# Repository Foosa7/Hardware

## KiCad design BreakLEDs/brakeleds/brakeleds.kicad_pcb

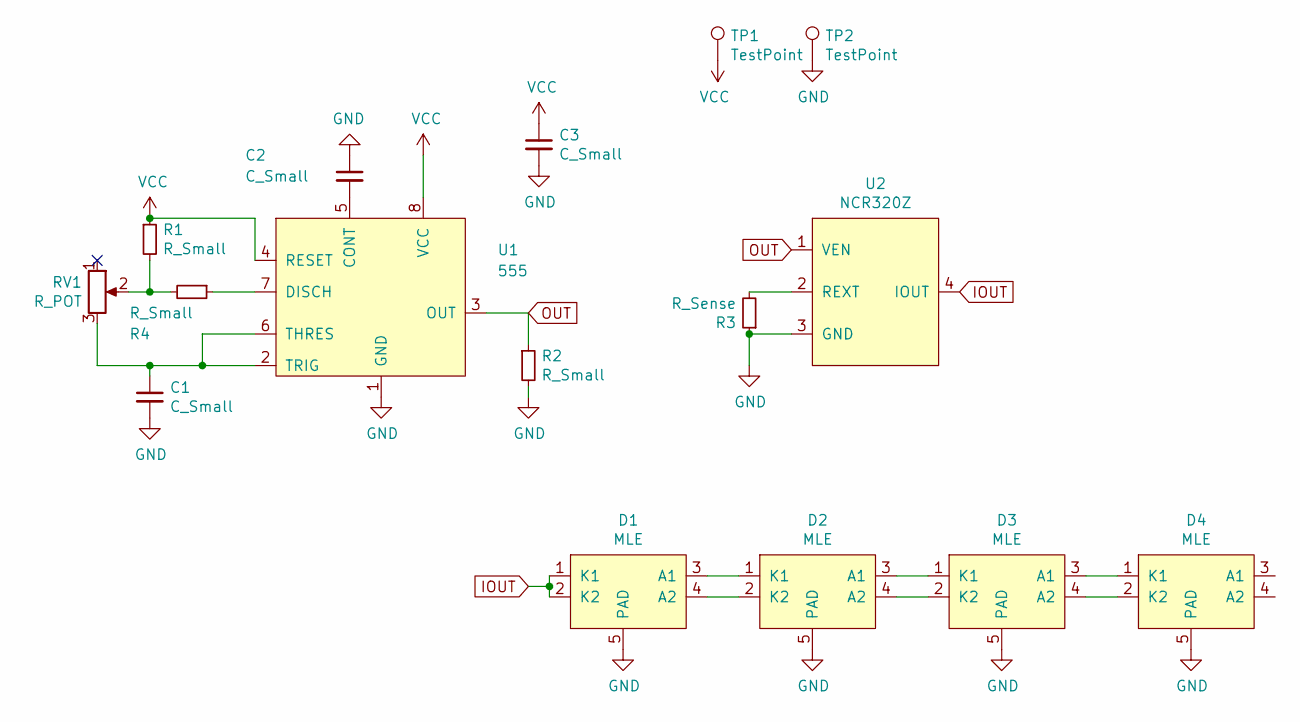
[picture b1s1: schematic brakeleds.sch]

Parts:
C1, C2, C3: C_Small; C_0603_1608Metric
D1, D2, D3, D4: MLE; PLCC-4
R1, R2, R4: R_Small; R_0603_1608Metric
R3: R_Sense; R_0805_2012Metric
RV1: R_POT; potentiometer
TP1, TP2: TestPoint; SolderWirePad_1x01_SMD_1x2mm
U1: 555; TSSOP-8_4.4x3mm_P0.65mm
U2: NCR320Z; SOT-223

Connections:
GND: C1.2, C2.1, C3.2, D1.5 (PAD), D2.5 (PAD), D3.5 (PAD), D4.5 (PAD), R2.2, R3.1, TP2.1, U1.1 (GND), U2.3 (GND)
IOUT: D1.1 (K1), D1.2 (K2), U2.4 (IOUT)
unnamed: C1.1, RV1.3, U1.2 (TRIG), U1.6 (THRES)
unnamed: C2.2, U1.5 (CONT)
unnamed: D1.3 (A1), D2.1 (K1)
unnamed: D1.4 (A2), D2.2 (K2)
unnamed: D2.3 (A1), D3.1 (K1)
unnamed: D2.4 (A2), D3.2 (K2)
unnamed: D3.3 (A1), D4.1 (K1)
unnamed: D3.4 (A2), D4.2 (K2)
unnamed: R1.2, R4.2, RV1.2
unnamed: R3.2, U2.2 (REXT)
unnamed: R4.1, U1.7 (DISCH)
OUT: R2.1, U1.3 (OUT), U2.1 (VEN)
VCC: C3.1, R1.1, TP1.1, U1.4 (RESET), U1.8 (VCC)

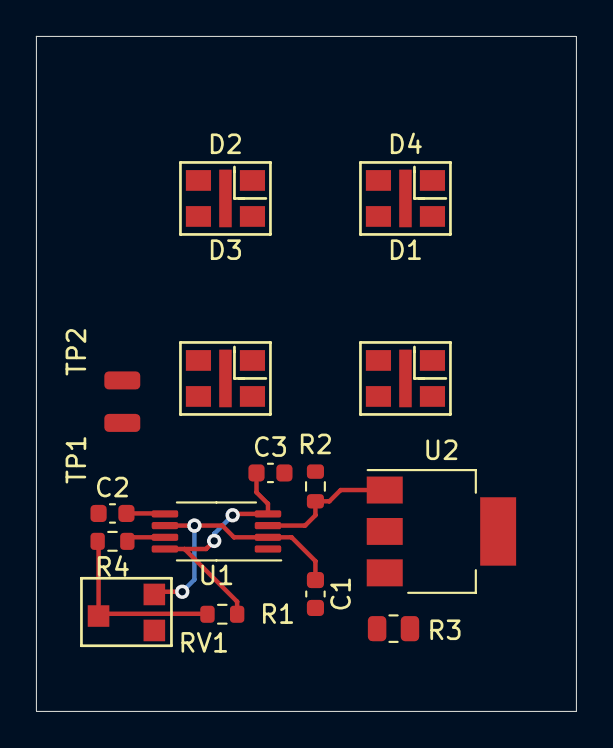
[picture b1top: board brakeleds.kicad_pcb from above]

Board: 2 copper layers, 30.0 x 37.5 mm, 16 parts (0 on the bottom side), 15 nets.

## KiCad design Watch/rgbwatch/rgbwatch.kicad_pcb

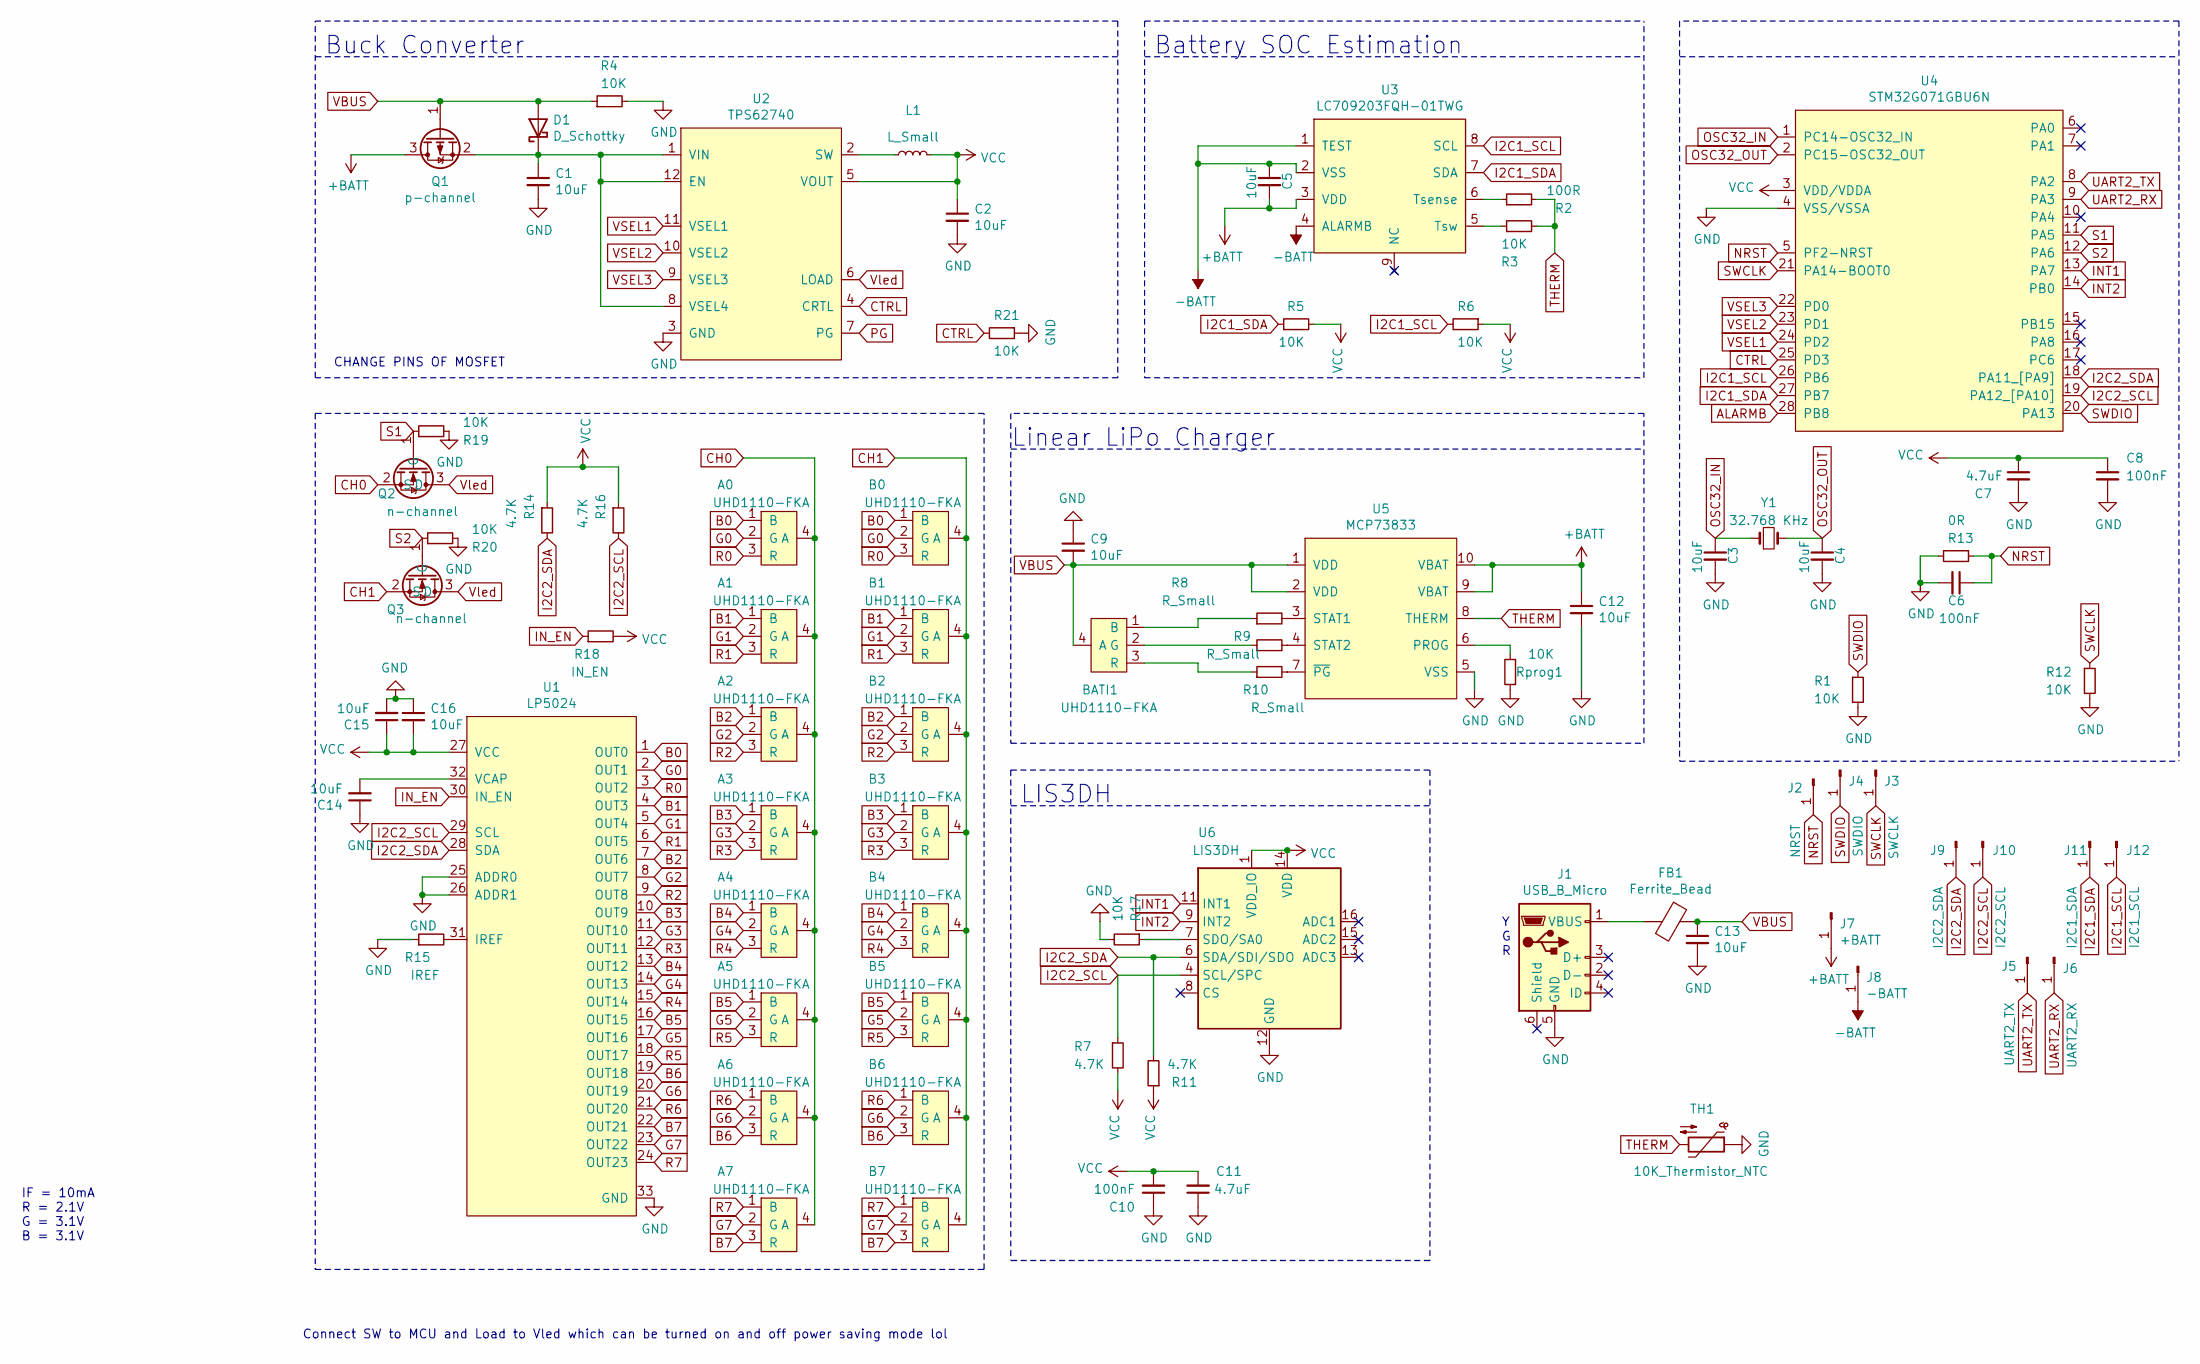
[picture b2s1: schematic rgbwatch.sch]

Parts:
A0, A1, A2, A3, A4, A5, A6, A7: UHD1110-FKA
B0, B1, B2, B3, B4, B5, B6, B7: UHD1110-FKA
BATI1: UHD1110-FKA
C1, C2, C3, C4, C5, C9, C12, C13, C14, C15, C16: 10uF; C_0402_1005Metric
C6, C8, C10: 100nF; C_0402_1005Metric
C7, C11: 4.7uF; C_0402_1005Metric
D1: D_Schottky; D_SOD-123
FB1: Ferrite_Bead; L_0603_1608Metric
J1: USB_B_Micro; USB_Micro-B_Amphenol_10104110_Horizontal
J2: NRST; SolderWirePad_1x01_SMD_1x2mm
J3: SWCLK; SolderWirePad_1x01_SMD_1x2mm
J4: SWDIO; SolderWirePad_1x01_SMD_1x2mm
J5: UART2_TX; SolderWirePad_1x01_SMD_1x2mm
J6: UART2_RX; SolderWirePad_1x01_SMD_1x2mm
J7: +BATT; SolderWirePad_1x01_SMD_1x2mm
J8: -BATT; SolderWirePad_1x01_SMD_1x2mm
J9: I2C2_SDA; SolderWirePad_1x01_SMD_1x2mm
J10: I2C2_SCL; SolderWirePad_1x01_SMD_1x2mm
J11: I2C1_SDA; SolderWirePad_1x01_SMD_1x2mm
J12: I2C1_SCL; SolderWirePad_1x01_SMD_1x2mm
L1: L_Small; L_0805_2012Metric
Q1: p-channel; SOT-23
Q2, Q3: n-channel; SOT-23
R1, R3, R4, R5, R6, R12, R17, R19, R20, R21: 10K; R_0402_1005Metric
R2: 100R; R_0402_1005Metric
R7, R11, R14, R16: 4.7K; R_0402_1005Metric
R8, R9, R10: R_Small; R_0402_1005Metric
R13: 0R; R_0402_1005Metric
R15: IREF; R_0402_1005Metric
R18: IN_EN; R_0402_1005Metric
Rprog1: 10K; R_0402_1005Metric
TH1: 10K_Thermistor_NTC; R_0603_1608Metric
U1: LP5024; QFN-32_EP_4.4x4.4_Pitch0.4mm
U2: TPS62740; WSON-12-1EP_3x2mm_P0.5mm_EP1x2.65_ThermalVias
U3: LC709203FQH−01TWG; WDFN-8
U4: STM32G071GBU6N; QFN-28_EP_5.3x5.3_Pitch0.5mm
U5: MCP73833; DFN-10-1EP_3x3mm_P0.5mm_EP1.65x2.38mm_ThermalVias
U6: LIS3DH; LGA-16_3x3mm_P0.5mm_LayoutBorder3x5y
Y1: 32.768 KHz; Crystal_SMD_2012-2Pin_2.0x1.2mm

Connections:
+BATT: C5.2, C12.1, J7.1, Q1.3 (D), U3.3 (VDD), U5.9 (VBAT), U5.10 (VBAT)
-BATT: C5.1, J8.1, U3.1 (TEST), U3.2 (VSS), U3.4 (ALARMB)
ALARMB: U4.28 (PB8)
B0: A0.1 (B), B0.1 (B), U1.1 (OUT0)
B1: A1.1 (B), B1.1 (B), U1.4 (OUT3)
B2: A2.1 (B), B2.1 (B), U1.7 (OUT6)
B3: A3.1 (B), B3.1 (B), U1.10 (OUT9)
B4: A4.1 (B), B4.1 (B), U1.13 (OUT12)
B5: A5.1 (B), B5.1 (B), U1.16 (OUT15)
B6: A6.3 (R), B6.3 (R), U1.19 (OUT18)
B7: A7.3 (R), B7.3 (R), U1.22 (OUT21)
CH0: A0.4 (A), A1.4 (A), A2.4 (A), A3.4 (A), A4.4 (A), A5.4 (A), A6.4 (A), A7.4 (A), Q2.2 (S)
CH1: B0.4 (A), B1.4 (A), B2.4 (A), B3.4 (A), B4.4 (A), B5.4 (A), B6.4 (A), B7.4 (A), Q3.2 (S)
CTRL: R21.2, U2.4 (CRTL), U4.25 (PD3)
G0: A0.2 (G), B0.2 (G), U1.2 (OUT1)
G1: A1.2 (G), B1.2 (G), U1.5 (OUT4)
G2: A2.2 (G), B2.2 (G), U1.8 (OUT7)
G3: A3.2 (G), B3.2 (G), U1.11 (OUT10)
G4: A4.2 (G), B4.2 (G), U1.14 (OUT13)
G5: A5.2 (G), B5.2 (G), U1.17 (OUT16)
G6: A6.2 (G), B6.2 (G), U1.20 (OUT19)
G7: A7.2 (G), B7.2 (G), U1.23 (OUT22)
GND: C1.2, C2.2, C3.2, C4.2, C6.2, C7.2, C8.2, C9.1, C10.1, C11.1, C12.2, C13.2, C14.1, C15.2, C16.1, J1.5 (GND), R1.2, R4.2, R12.2, R13.2, R15.1, R17.2, R19.2, R20.2, R21.1, Rprog1.1, TH1.1, U1.25 (ADDR0), U1.26 (ADDR1), U1.33 (GND), U2.3 (GND), U4.4 (VSS/VSSA), U5.5 (VSS), U6.5 (GND), U6.10 (GND), U6.12 (GND)
I2C1_SCL: J12.1, R6.2, U3.8 (SCL), U4.26 (PB6)
I2C1_SDA: J11.1, R5.1, U3.7 (SDA), U4.27 (PB7)
I2C2_SCL: J10.1, R7.1, R16.2, U1.29 (SCL), U4.19 (PA12_[PA10]), U6.4 (SCL/SPC)
I2C2_SDA: J9.1, R11.2, R14.2, U1.28 (SDA), U4.18 (PA11_[PA9]), U6.6 (SDA/SDI/SDO)
INT1: U4.13 (PA7), U6.11 (INT1)
INT2: U4.14 (PB0), U6.9 (INT2)
IN_EN: R18.1, U1.30 (IN_EN)
NRST: C6.1, J2.1, R13.1, U4.5 (PF2-NRST)
unnamed: BATI1.1 (B), R8.1
unnamed: BATI1.2 (G), R9.1
unnamed: BATI1.3 (R), R10.1
unnamed: C1.1, D1.1 (K), Q1.2 (S), U2.1 (VIN), U2.8 (VSEL4), U2.12 (EN)
unnamed: C14.2, U1.32 (VCAP)
unnamed: FB1.2, J1.1 (VBUS)
unnamed: L1.1, U2.2 (SW)
unnamed: R2.1, U3.6 (Tsense)
unnamed: R3.1, U3.5 (Tsw)
unnamed: R8.2, U5.3 (STAT1)
unnamed: R9.2, U5.4 (STAT2)
unnamed: R10.2, U5.7 (~PG)
unnamed: R15.2, U1.31 (IREF)
unnamed: R17.1, U6.7 (SDO/SA0)
unnamed: Rprog1.2, U5.6 (PROG)
OSC32_IN: C3.1, U4.1 (PC14-OSC32_IN), Y1.1
OSC32_OUT: C4.1, U4.2 (PC15-OSC32_OUT), Y1.2
PG: U2.7 (PG)
R0: A0.3 (R), B0.3 (R), U1.3 (OUT2)
R1: A1.3 (R), B1.3 (R), U1.6 (OUT5)
R2: A2.3 (R), B2.3 (R), U1.9 (OUT8)
R3: A3.3 (R), B3.3 (R), U1.12 (OUT11)
R4: A4.3 (R), B4.3 (R), U1.15 (OUT14)
R5: A5.3 (R), B5.3 (R), U1.18 (OUT17)
R6: A6.1 (B), B6.1 (B), U1.21 (OUT20)
R7: A7.1 (B), B7.1 (B), U1.24 (OUT23)
S1: Q2.1 (G), R19.1, U4.11 (PA5)
S2: Q3.1 (G), R20.1, U4.12 (PA6)
SWCLK: J3.1, R12.1, U4.21 (PA14-BOOT0)
SWDIO: J4.1, R1.1, U4.20 (PA13)
THERM: R2.2, R3.2, TH1.2, U5.8 (THERM)
UART2_RX: J6.1, U4.9 (PA3)
UART2_TX: J5.1, U4.8 (PA2)
VBUS: BATI1.4 (A), C9.2, C13.1, D1.2 (A), FB1.1, Q1.1 (G), R4.1, U5.1 (VDD), U5.2 (VDD)
VCC: C2.1, C7.1, C8.1, C10.2, C11.2, C15.1, C16.2, L1.2, R5.2, R6.1, R7.2, R11.1, R14.1, R16.1, R18.2, U1.27 (VCC), U2.5 (VOUT), U4.3 (VDD/VDDA), U6.1 (VDD_IO), U6.14 (VDD)
VSEL1: U2.11 (VSEL1), U4.24 (PD2)
VSEL2: U2.10 (VSEL2), U4.23 (PD1)
VSEL3: U2.9 (VSEL3), U4.22 (PD0)
Vled: Q2.3 (D), Q3.3 (D), U2.6 (LOAD)

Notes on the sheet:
Buck Converter
Battery SOC Estimation
IF = 10mA R = 2.1V G = 3.1V B = 3.1V
Connect SW to MCU and Load to Vled which can be turned on and off power saving mode lol
CHANGE PINS OF MOSFET
Linear LiPo Charger
Y G R
LIS3DH

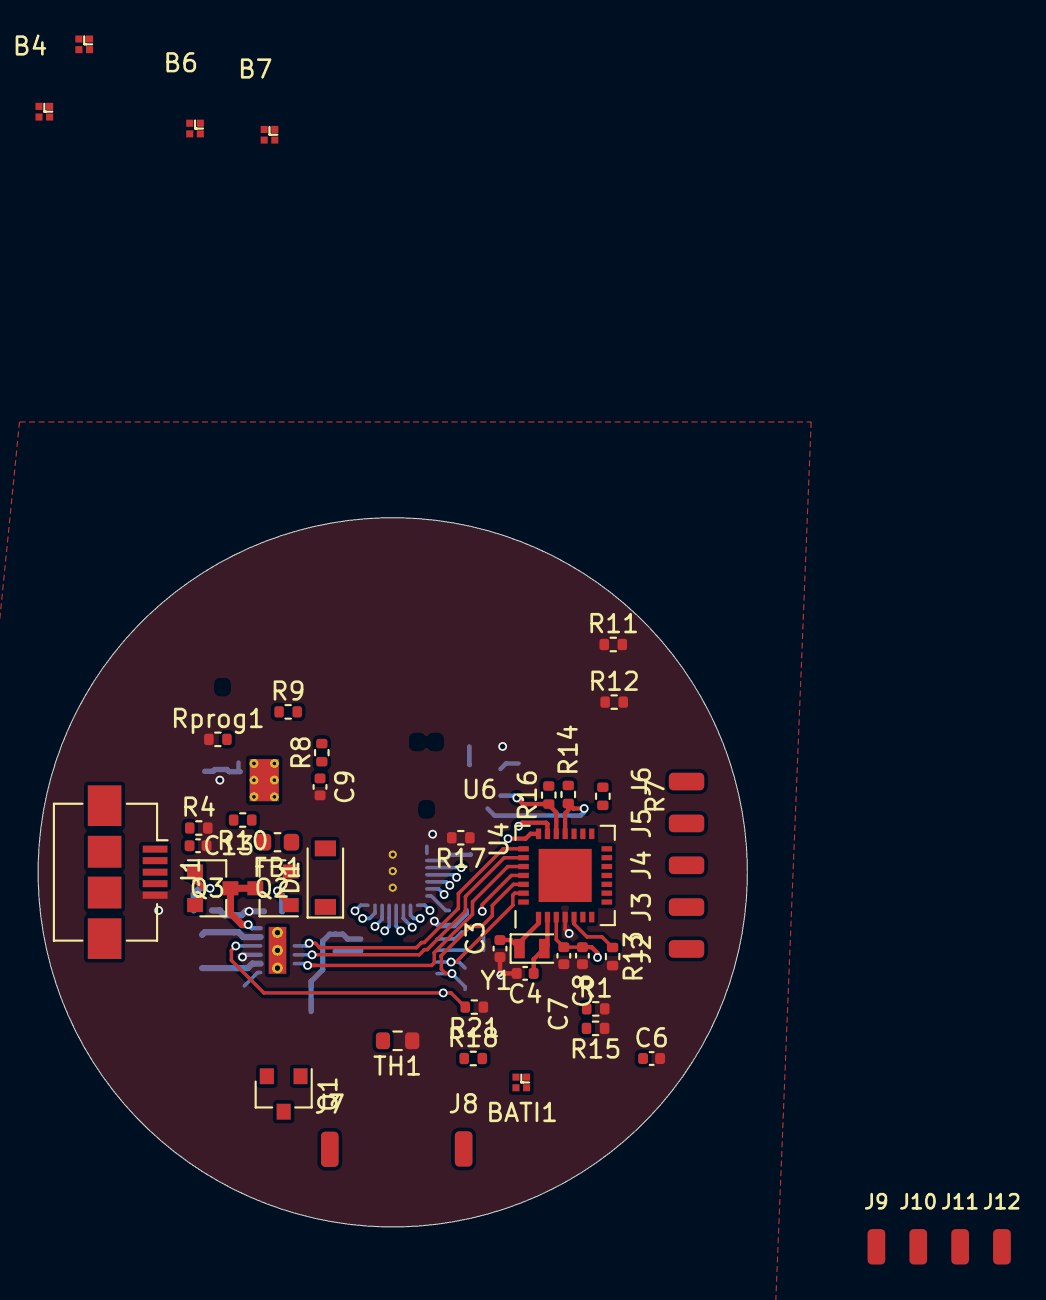
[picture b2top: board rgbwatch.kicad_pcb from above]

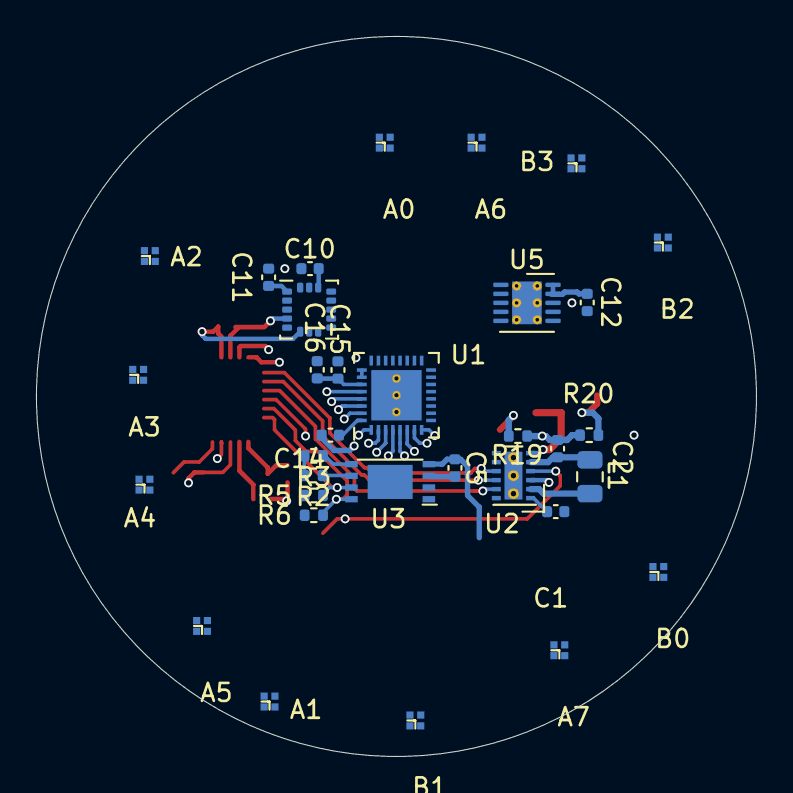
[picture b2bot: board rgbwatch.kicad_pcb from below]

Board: 4 copper layers, 40.0 x 40.0 mm, 81 parts (33 on the bottom side), 68 nets.
